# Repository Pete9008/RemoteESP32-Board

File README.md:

# RemoteESP32-Board
Stand alone 12V ESP32 module with SD card and RS485 and CAN bus interfaces

# Usage
This board is intended to be used with this firmware: https://github.com/Pete9008/esp32-web-interface/tree/Remote485 which currently supports use of the RS485 interface in either half or full duplex mode.

The BOM reflects the build for full duplex (4-wire RS485).  To use this the following line in the firmware needs to be commented out:
line88 - //#define RS485_HALF_DUPLEX 1

To use in half duplex mode (2-wire RS485) resistors R23 and R24 must have zero ohm links fitted (Note - This mode is not compatible with the standard OpenInverter firmware.

The firmware does not currently support CAN bus operation.  The CAN interface is currently untested.

# Powering
The board needs a 12V power supply connected on header J4.

0V connects to Pin-2
12V connects to Pin-1 (WiFi only mode)
12V connects to Pin-3 (SD card logging mode)

If power is supplied on Pin-1 then SD card logging is disabled (SD card files can still be read over the web interface though).

If power is supplied on Pin-3 then SD card logging will start (but only while there is no connection on the WiFi).

Note - Not all OpenInverter firmware versions support logging.

# SD Card Interface
The SD card uses the SDIO interface to allow high speed logging.  This requires a pull up on the D2 line (GPIO12) which prevents ESP32-WROOM-32E modules from booting from internal flash.

If the SD card is not used do not populate R9 (D2 pullup).

If the SD card is required then the module must have the flash voltage selection eFuses burned BEFORE resistor R9 is fitted.  See https://docs.espressif.com/projects/esp-idf/en/latest/esp32/api-reference/peripherals/sd_pullup_requirements.html for details of the fuse burning process.

# Programming Interface
Header J3 provides a programming interface for the board.  An external USB to TTL 232 converter dongle is required to connect to this header.  To place the ESP32 into programming mode pins 1 and 2 of the header must be linked.  Pin-6 on the header can then either be grounded manually to reset the ESP32 and enter programming mode or can connected to RTS on the dongle (a reset will then be generated automatically by the esptool programming software).  The Tx line on the dongle connects to header Pin-4 and the Rx line to header Pin-5.  Header Pin-1 should connect to dongle 0V/GND.

Power during programming must be supplied by connecting 12V on the power header J4.

# Enclosure
Two versions of a 3D printable enclosure are included:
RemoteESP32_Enclosure_NoBat.FCStd - Slim enclosure but without enough space for the RTC backup battery.
RemoteESP32_Enclosure_Bat.FCStd - Larger enclosure with space for the RTC battery.

Both are in FreeCAD format.  .stl files for the enclosure base and lid are also included.

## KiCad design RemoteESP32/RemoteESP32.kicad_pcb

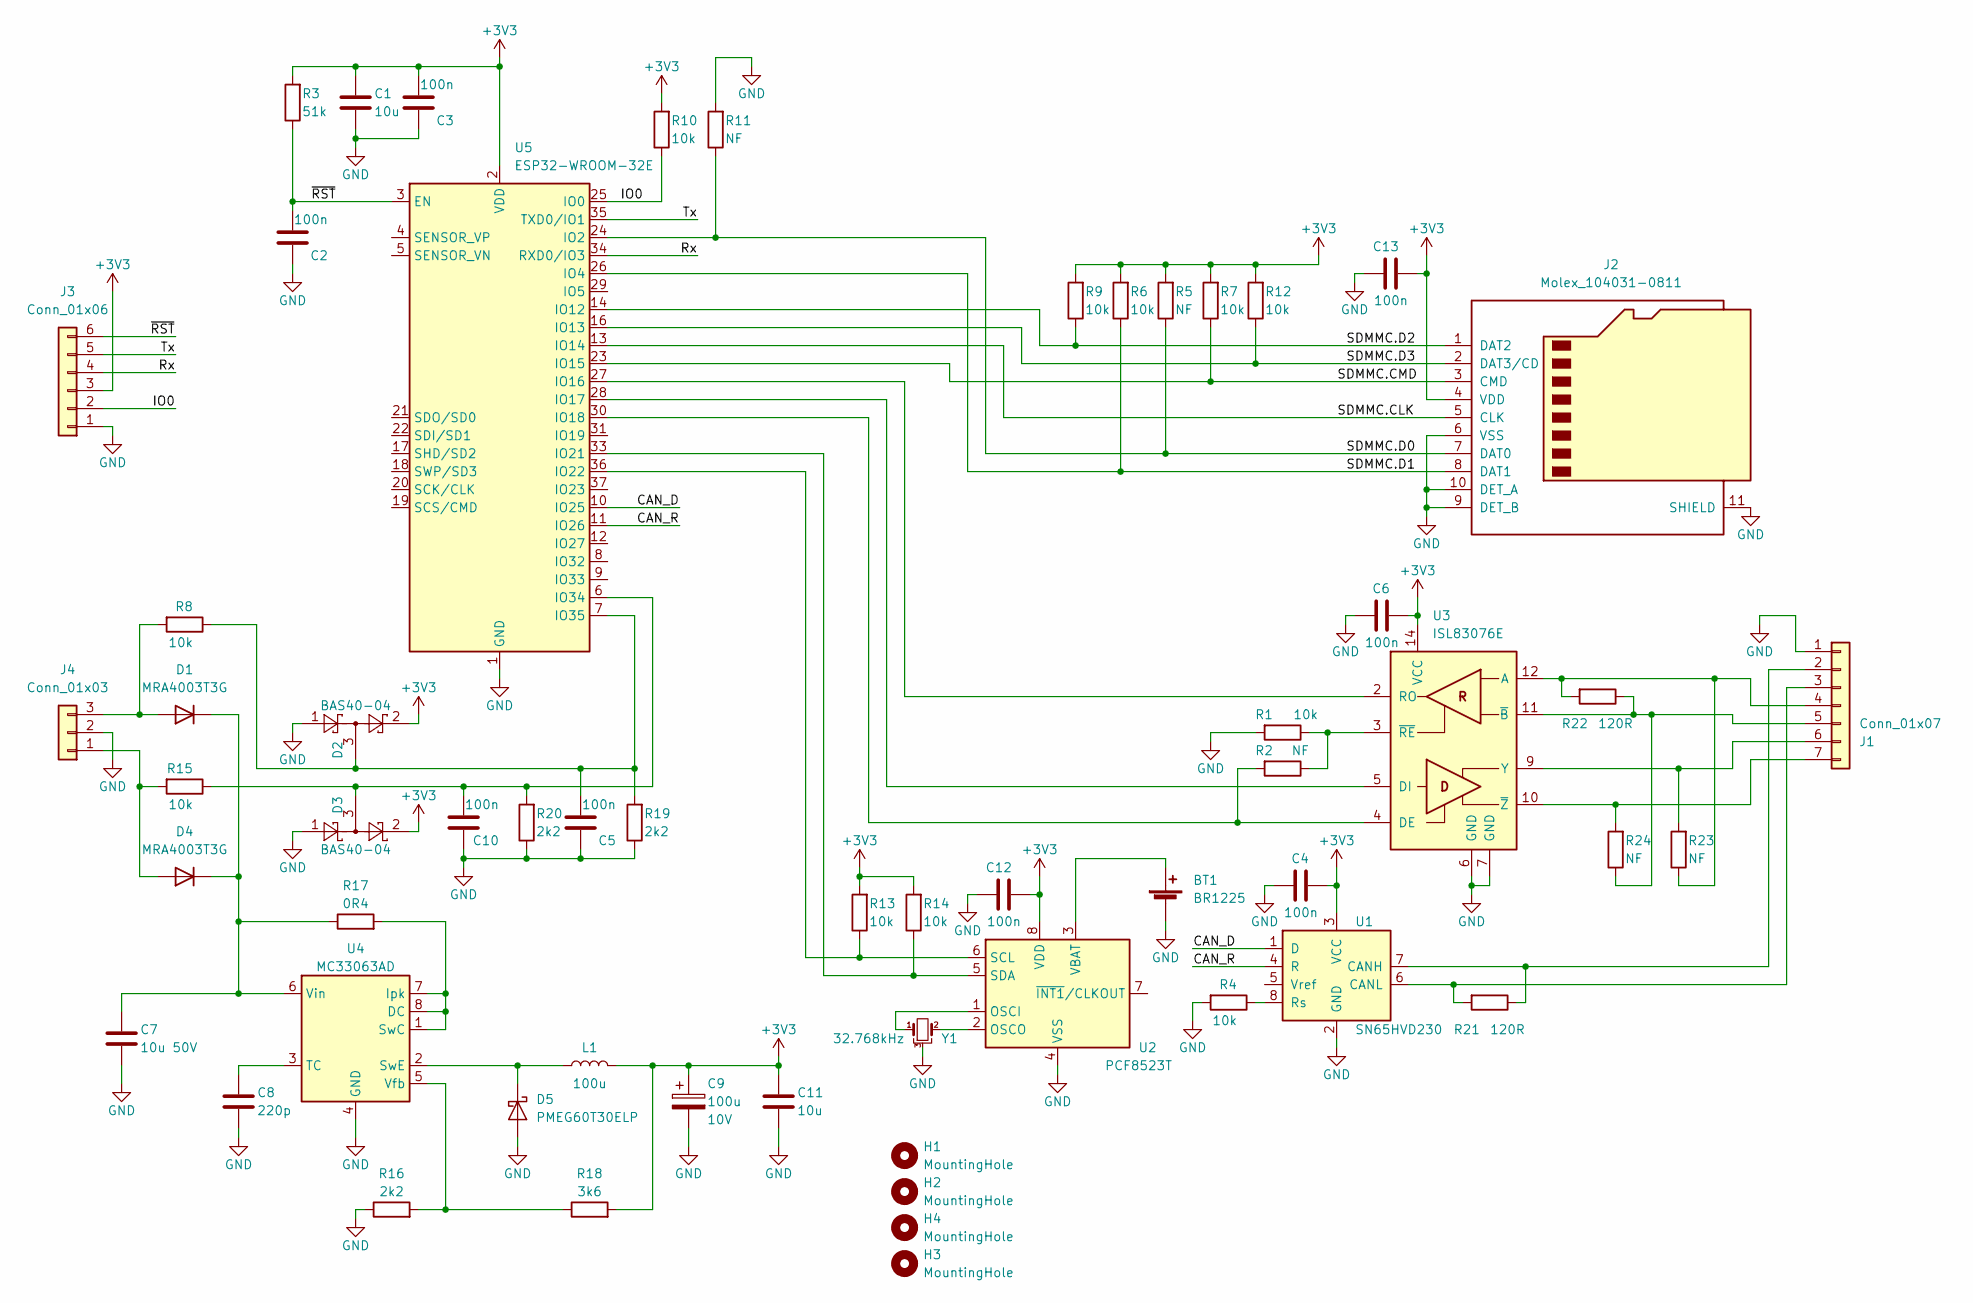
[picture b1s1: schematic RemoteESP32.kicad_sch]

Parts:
BT1: BR1225; Battery_Panasonic_CR1220-VCN_Vertical_CircularHoles
C1, C11: 10u; C_1206_3216Metric; Voltage 50V; Part CL31A106MBHNNNE
C2, C3, C4, C5, C6, C10, C12, C13: 100n; C_0603_1608Metric
C7: 10u 50V; C_1206_3216Metric; Part CL31A106MBHNNNE
C8: 220p; C_0603_1608Metric
C9: 100u; CP_EIA-7343-31_Kemet-D; Voltage 10V
D1, D4: MRA4003T3G; D_SMA
D2, D3: BAS40-04; SOT-23; Part BAS40-04
D5: PMEG60T30ELP; D_SOD-128; Part PMEG60T30ELP
H1, H2, H3, H4: MountingHole; MountingHole_2.2mm_M2_DIN965
J1: Conn_01x07; Molex_KK-254_AE-6410-07A_1x07_P2.54mm_Vertical
J2: Molex_104031-0811; microSD_HC_Molex_104031-0811; Part 104031-0811
J3: Conn_01x06; PinHeader_1x06_P2.54mm_Vertical
J4: Conn_01x03; Molex_KK-254_AE-6410-03A_1x03_P2.54mm_Vertical
L1: 100u; L_Bourns_SRR1260; Part SRR1260-101M
R1, R4, R6, R7, R8, R9, R10, R12, R13, R14, R15: 10k; R_0603_1608Metric
R2, R5, R11, R23, R24: NF; R_0603_1608Metric
R3: 51k; R_0603_1608Metric
R16, R19, R20: 2k2; R_0603_1608Metric
R17: 0R4; R_1206_3216Metric
R18: 3k6; R_0603_1608Metric
R21, R22: 120R; R_0603_1608Metric
U1: SN65HVD230; SOIC-8_3.9x4.9mm_P1.27mm
U2: PCF8523T; SOIC-8_3.9x4.9mm_P1.27mm
U3: ISL83076E; SO-14_3.9x8.65mm_P1.27mm
U4: MC33063AD; SOIC-8_3.9x4.9mm_P1.27mm; Part MC33063AD
U5: ESP32-WROOM-32E; ESP32-WROOM-32
Y1: 32.768kHz; Crystal_AT310_D3.0mm_L10.0mm_Horizontal_1EP_style2

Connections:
+3V3: C1.1, C3.2, C4.2, C6.2, C9.1, C11.1, C12.2, C13.2, D2.2, D3.2, J2.4 (VDD), J3.3, L1.2, R3.2, R5.2, R6.2, R7.2, R9.2, R10.2, R12.2, R13.2, R14.2, R18.2, U1.3 (VCC), U2.8 (VDD), U3.14 (VCC), U5.2 (VDD)
/CAN_D: U1.1 (D), U5.10 (IO25)
/CAN_R: U1.4 (R), U5.11 (IO26)
/IO0: J3.2, R10.1, U5.25 (IO0)
/Rx: J3.4, U5.34 (RXD0/IO3)
/SDMMC.CLK: J2.5 (CLK), U5.13 (IO14)
/SDMMC.CMD: J2.3 (CMD), R7.1, U5.23 (IO15)
/SDMMC.D0: J2.7 (DAT0), R5.1, R11.1, U5.24 (IO2)
/SDMMC.D1: J2.8 (DAT1), R6.1, U5.26 (IO4)
/SDMMC.D2: J2.1 (DAT2), R9.1, U5.14 (IO12)
/SDMMC.D3: J2.2 (DAT3/CD), R12.1, U5.16 (IO13)
/Tx: J3.5, U5.35 (TXD0/IO1)
/~RST: C2.2, J3.6, R3.1, U5.3 (EN)
GND: BT1.2 (-), C1.2, C2.1, C3.1, C4.1, C5.1, C6.1, C7.2, C8.2, C9.2, C10.1, C11.2, C12.1, C13.1, D2.1, D3.1, D5.2 (A), J1.1, J2.6 (VSS), J2.9 (DET_B), J2.10 (DET_A), J2.11 (SHIELD), J3.1, J4.2, R1.2, R4.2, R11.2, R16.1, R19.1, R20.1, U1.2 (GND), U2.4 (VSS), U3.6 (GND), U3.7 (GND), U4.4 (GND), U5.1 (GND), U5.15 (GND), U5.38 (GND), U5.39 (GND), Y1.3
unnamed: BT1.1 (+), U2.3 (VBAT)
unnamed: C5.2, D2.3, R8.1, R19.2, U5.7 (IO35)
unnamed: C7.1, D1.1 (K), D4.1 (K), R17.1, U4.6 (Vin)
unnamed: C8.1, U4.3 (TC)
unnamed: C10.2, D3.3, R15.1, R20.2, U5.6 (IO34)
unnamed: D1.2 (A), J4.3, R8.2
unnamed: D4.2 (A), J4.1, R15.2
unnamed: D5.1 (K), L1.1, U4.2 (SwE)
unnamed: J1.2, R21.1, U1.7 (CANH)
unnamed: J1.3, R21.2, U1.6 (CANL)
unnamed: J1.4, R22.2, R23.1, U3.12 (A)
unnamed: J1.5, R22.1, R24.1, U3.11 (~B)
unnamed: J1.6, R23.2, U3.9 (Y)
unnamed: J1.7, R24.2, U3.10 (~Z)
unnamed: R1.1, R2.1, U3.3 (~RE)
unnamed: R2.2, U3.4 (DE), U5.30 (IO18)
unnamed: R4.1, U1.8 (Rs)
unnamed: R13.1, U2.6 (SCL), U5.36 (IO22)
unnamed: R14.1, U2.5 (SDA), U5.33 (IO21)
unnamed: R16.2, R18.1, U4.5 (Vfb)
unnamed: R17.2, U4.1 (SwC), U4.7 (Ipk), U4.8 (DC)
unnamed: U2.1 (OSCI), Y1.1
unnamed: U2.2 (OSCO), Y1.2
unnamed: U3.2 (RO), U5.27 (IO16)
unnamed: U3.5 (DI), U5.28 (IO17)

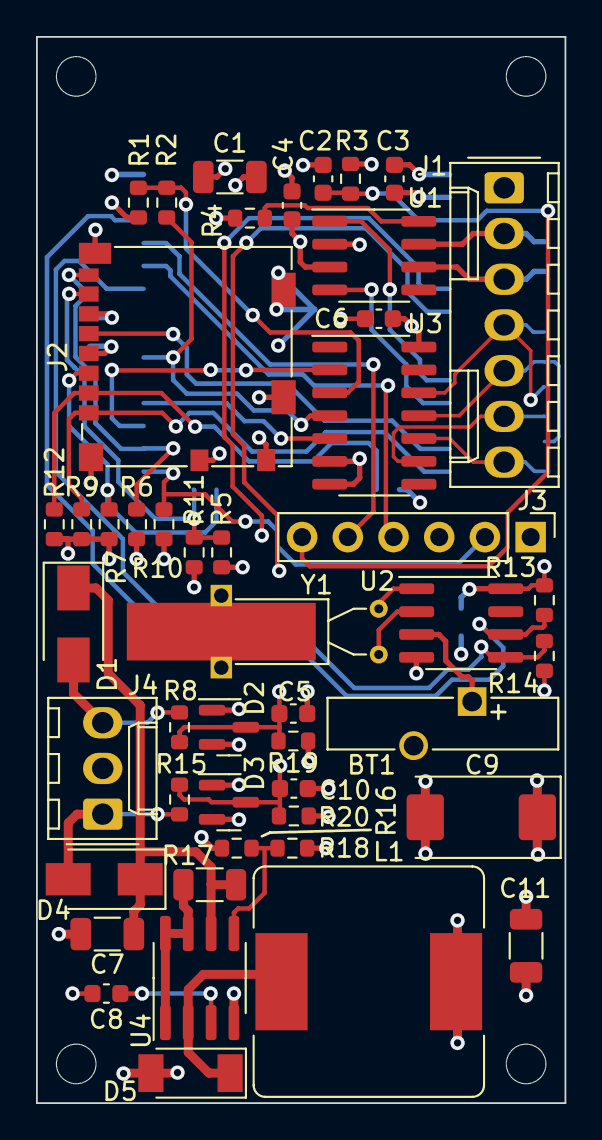
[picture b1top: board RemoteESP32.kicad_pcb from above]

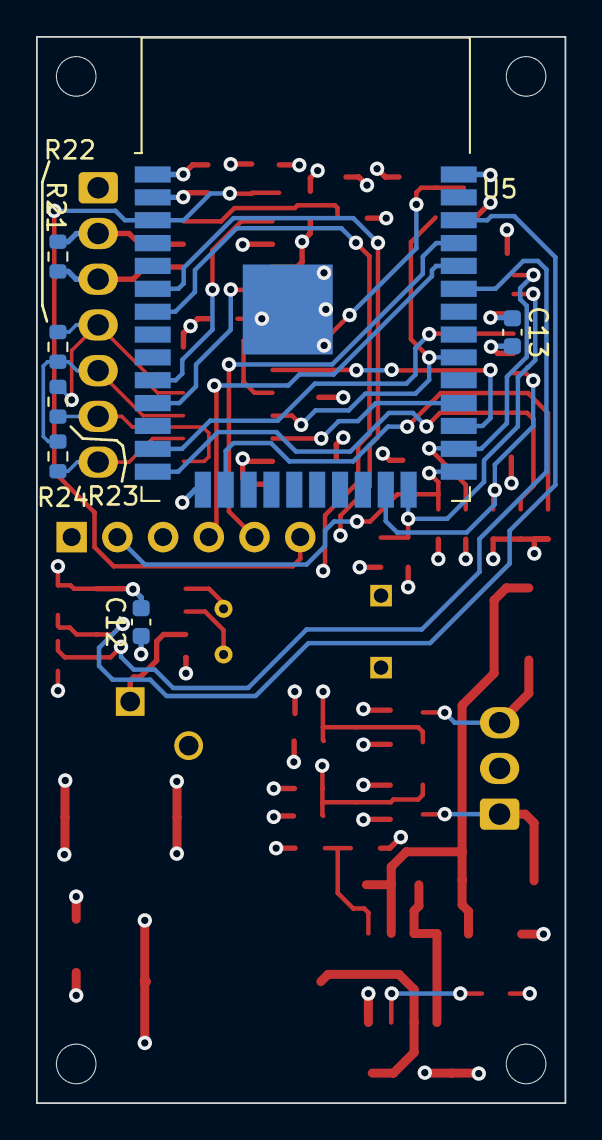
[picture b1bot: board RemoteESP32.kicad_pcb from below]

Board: 4 copper layers, 29.4 x 59.2 mm, 58 parts (7 on the bottom side), 39 nets.

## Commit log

2023-03-04 Added .csv BOM file
2023-03-12 Added enclosure model
